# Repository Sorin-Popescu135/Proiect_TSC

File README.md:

# OpenBook Project

## Overview
The OpenBook Project uses the **ESP32-C6 WROOM** module, which features:
- **Processor:** RISC-V single-core  
- **Memory:** 512 KB SRAM  
- **Connectivity:** Wi-Fi 6, Bluetooth 5, IEEE 802.15.4  
- **Interfaces:** GPIO, SPI, I2C, USB 2.0  

## Diagram

## ESP32-C6 Pin Descriptions

### Buttons
- **pin 3** → RESET  
- **pin 15** → IO/BOOT  
- **pin 23** → IO/RESET  

### Battery Level
- **pin 20** → pin 7 (SCL)  
- **pin 8** → pin 19 (SDA)  

### USB-C Connector & ESD Protection
- **pin 14** → pin 1 (USB_D+)  
- **pin 13** → pin 3 (USB_D-)  

### SD Card
- **pin 4** → pin 2 (SS_SD)  
- **pin 6** → pin 5 (SCK)  
- **pin 7** → pin 3 (MOSI)  
- **pin 27** → pin 7 (MISO)  

### BME688 Sensor
- **pin 17** → pin 2, 6, 8 (I2C_PW)  
- **pin 19** → pin 3 (SDA)  
- **pin 20** → pin 4 (SCL)  

### RTC Module DS3231SN
- **pin 8** → pin 3 (INT_RTC)  
- **pin 9** → pin 1 (32KHZ)  
- **pin 16** → pin 4 (RTC_RST)  
- **pin 19** → pin 15 (SDA)  
- **pin 20** → pin 16 (SCL)

## Hardware Description

| Part              | Description                                     |
|-------------------|-------------------------------------------------|
| DS3231SN          | -> high accuracy RTC                            |
| MAX17048G+T10     | -> battery fuel gauge                           |
| W25Q512JVEIQ      | -> serial NOR flash memory                      |
| FH34SRJ24S05SH99  | -> FFC connector                                |
| SI1308EDL-T1-GE3  | -> N-channel MOSFET                             |
| MCP73831          |-> charge management controller, single-cell     |
| USB4110           | -> USB 2.0 Type C connector                     |
| CPH3225A          | -> chip-type electric double-layer capacitor    |
| MBR0530           | -> surface-mount Schottky rectifier diode       |
| BME688            | -> environmental sensor                         |
| XC6220A331MR-G    | -> high-speed, low-dropout voltage regulator    |

## Bill of Materials

| Component Name       | Price (euro) | Link                                                                                                  |
|----------------------|--------------|--------------------------------------------------------------------------------------------------------|
| DS3231SN             | 14.91        | [Mouser](https://ro.mouser.com/ProductDetail/Analog-Devices-Maxim-Integrated/DS3231SN?qs=1eQvB6Dk1vhUlr8%2FOrV0Fw%3D%3D)  |
| MAX17048G+T10        | 4.28         | [Mouser](https://eu.mouser.com/ProductDetail/Analog-Devices-Maxim-Integrated/MAX17048G%2bT10?qs=D7PJwyCwLAoGnnn8jEPRBQ%3D%3D)    |
| W25Q512JVEIQ         | 5.84         | [Mouser](https://eu.mouser.com/ProductDetail/Winbond/W25Q512JVEIQ?qs=l7cgNqFNU1jw6svr3at6tA%3D%3D)    |
| FH34SRJ24S05SH99     | 2.60         | [Mouser](https://eu.mouser.com/ProductDetail/Hirose-Connector/FH34SRJ-24S-0.5SH99?qs=vcbW%252B4%252BSTIpKBl5ap9J8Fw%3D%3D)        |
| SI1308EDL-T1-GE3     | 0.41         | [Mouser](https://eu.mouser.com/ProductDetail/Vishay-Semiconductors/SI1308EDL-T1-GE3?qs=bX1%252BNvsK%2FBramh9tgpOaEw%3D%3D)         |
| MCP73831             | 0.70         | [Mouser](https://eu.mouser.com/ProductDetail/Microchip-Technology/MCP73831T-2ACI-OT?qs=yUQqVecv4qvbBQBGbHx0Mw%3D%3D)             |
| USB4110              | 1.18         | [Mouser](https://eu.mouser.com/ProductDetail/GCT/USB4110-GF-A?qs=KUoIvG%2F9IlYiZvIXQjyJeA%3D%3D)                          |
| CPH3225A             | 2.23         | [Mouser](https://eu.mouser.com/ProductDetail/Seiko-Semiconductors/CPH3225A?qs=3etwrb1wR%252BhUOph6lAO7eg%3D%3D)           |
| MBR0530              | 0.14         | [Mouser](https://eu.mouser.com/ProductDetail/Micro-Commercial-Components-MCC/MBR0530-TP?qs=KFo7JewZbUECRHkxGanrdg%3D%3D)        |
| BME688               | 9.86         | [Mouser](https://eu.mouser.com/ProductDetail/Bosch-Sensortec/BME688?qs=IS%252B4QmGtzzqQoVDscqwx3A%3D%3D)                    |
| XC6220A331MR-G       | 1.46         | [Mouser](https://eu.mouser.com/ProductDetail/Torex-Semiconductor/XC6220A331MR-G?qs=AsjdqWjXhJ8ZSWznL1J0gg%3D%3D)            |

## Additional Photos

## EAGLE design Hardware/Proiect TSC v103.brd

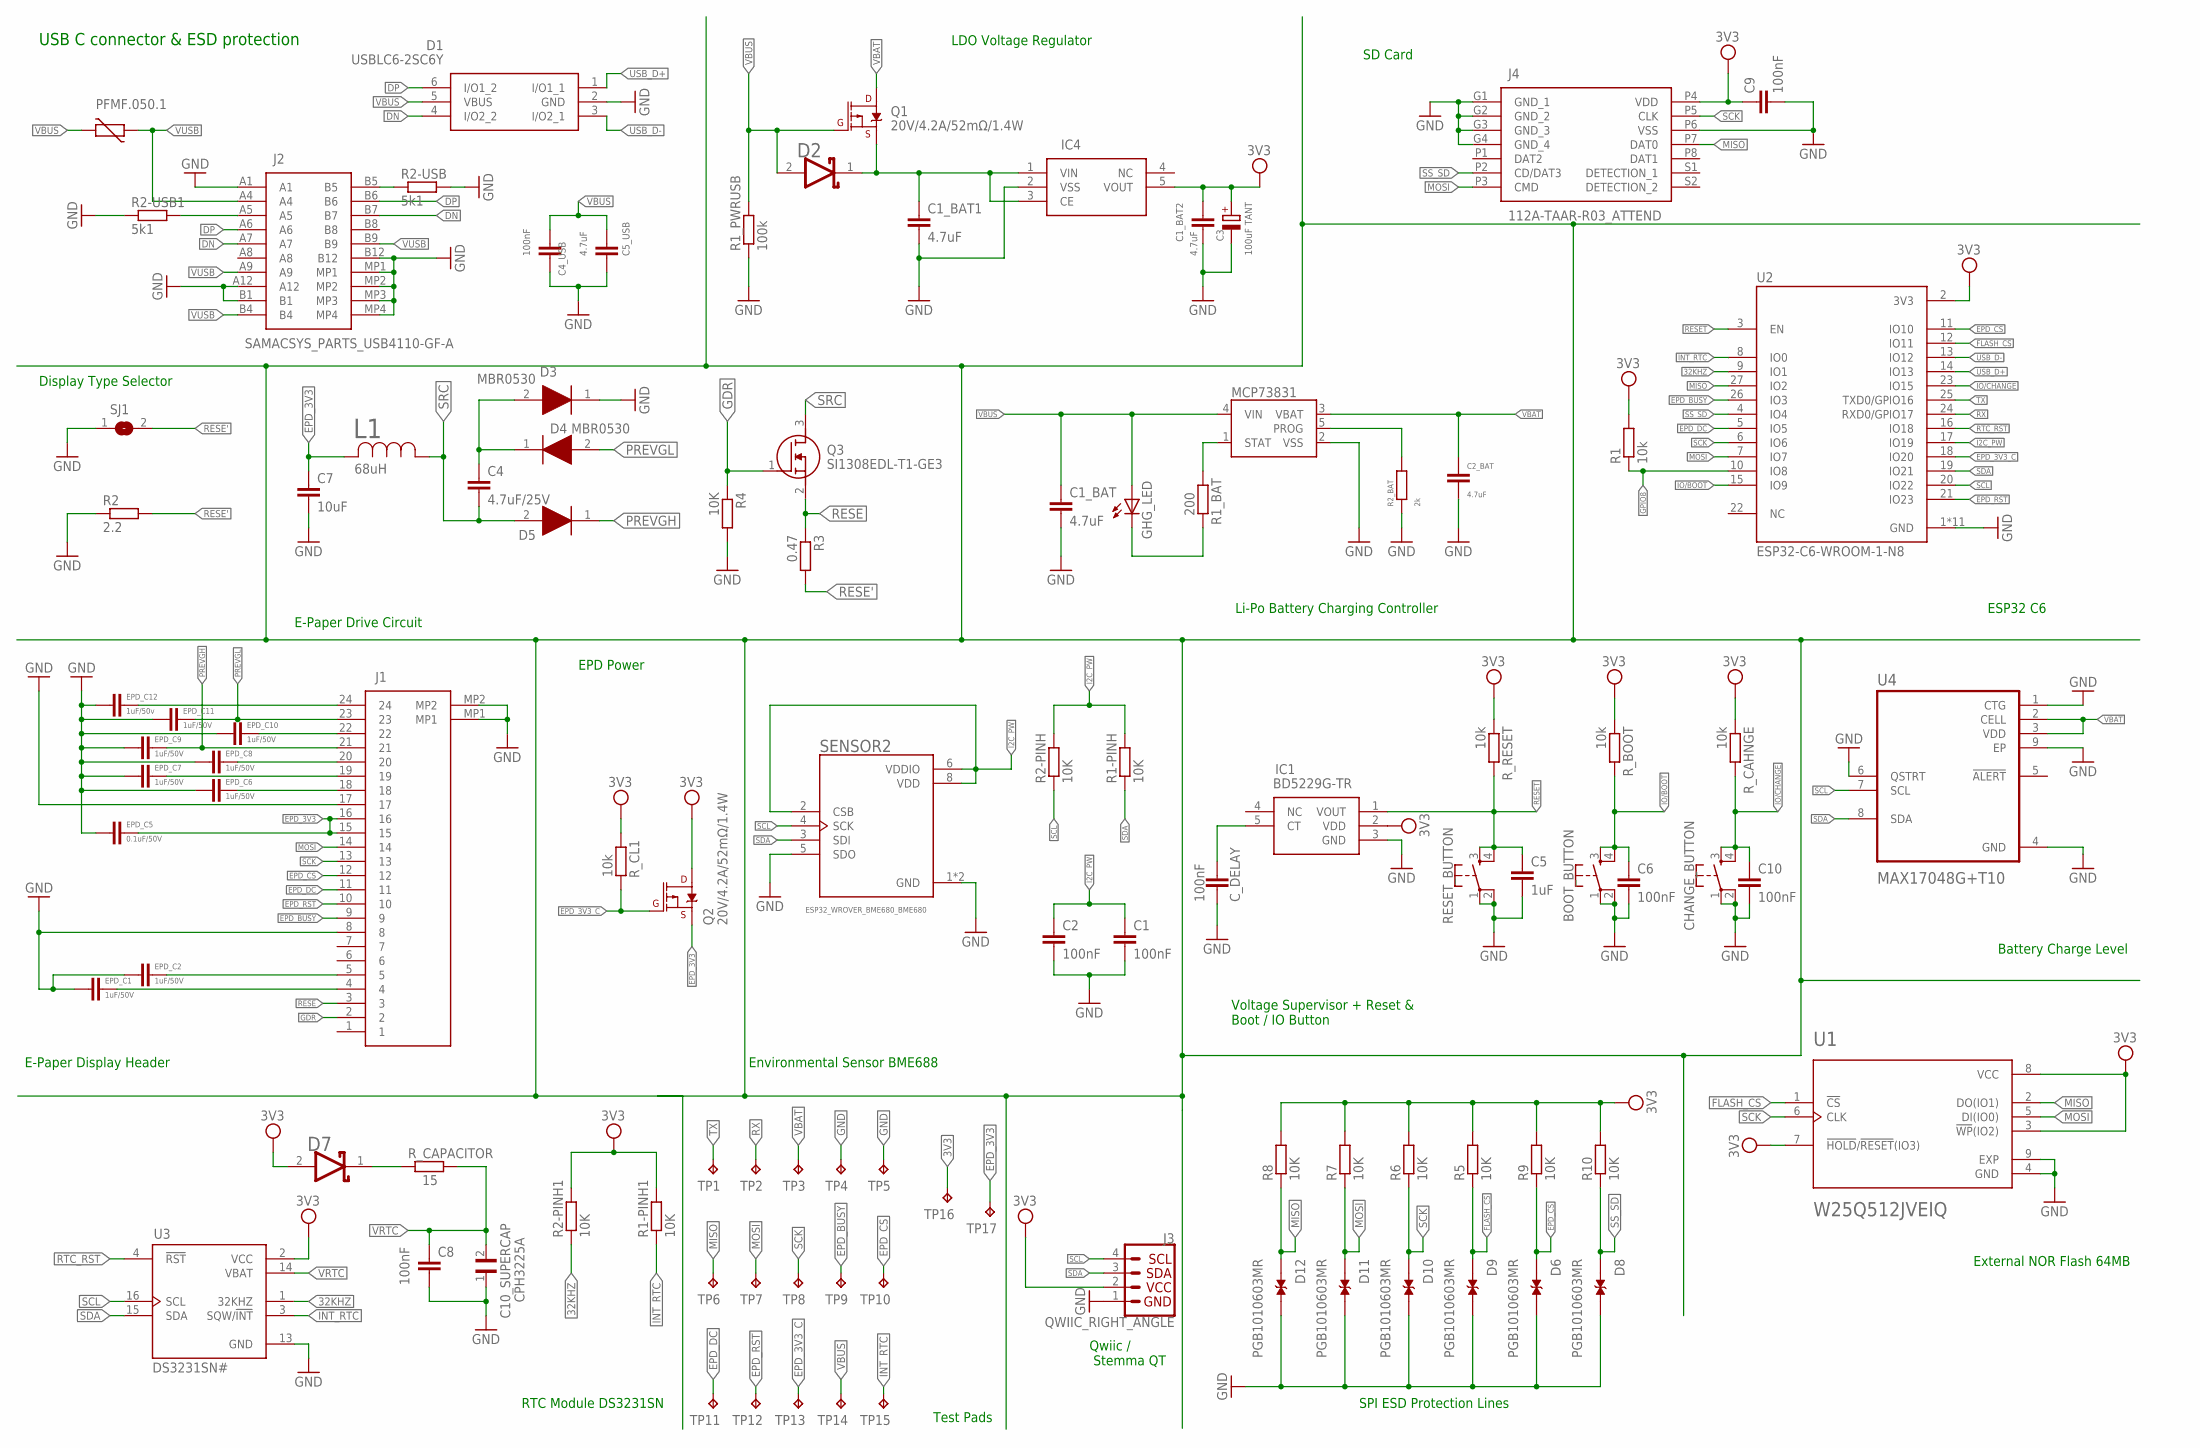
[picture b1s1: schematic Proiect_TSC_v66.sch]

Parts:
BOOT_BUTTON: BUTTON_CUSYOMV1; MYBUTTON
C1, C2, C9: 100nF; EAGLE-LTSPICE_C0402
C1_BAT, C2_BAT, C5_USB: 4.7uF; ESP32_WROVER_EAGLE-LTSPICE_C0402
C1_BAT1, C1_BAT2: 4.7uF; EAGLE-LTSPICE_C0402
C3: 100uF TANT; RCL_CT3528
C4: 4.7uF/25V; ESP32_WROVER_EAGLE-LTSPICE_C0402
C4_USB, C6, C8, C10: 100nF; ESP32_WROVER_EAGLE-LTSPICE_C0402
C5: 1uF; ESP32_WROVER_EAGLE-LTSPICE_C0402
C7: 10uF; EAGLE-LTSPICE_C0402
C10_SUPERCAP: CPH3225A; CAPCP3225X100N
CHANGE_BUTTON: BUTTON_CUSYOMV1; MYBUTTON
C_DELAY: 100nF; EAGLE-LTSPICE_C0402
D1: USBLC6-2SC6Y; SOT95P280X145-6N
D2, D7: ESP32_WROVER_AVX---SD0805S020S1R0_AVX_SD0805S020S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; ESP32_WROVER_AVX---SD0805S020S1R0_AVX_SD0805S020S1R0_0
D3, D4, D5: MBR0530; SOD3716X135N
D6, D8, D9, D10, D11, D12: PGB1010603MR; DIOC1608X36N
EPD_C1, EPD_C2, EPD_C6, EPD_C7, EPD_C8, EPD_C9, EPD_C10, EPD_C11: 1uF/50V; EAGLE-LTSPICE_C0402
EPD_C5: 0.1uF/50V; EAGLE-LTSPICE_C0402
EPD_C12: 1uF/50v; EAGLE-LTSPICE_C0402
GHG_LED: ADAFRUIT_LEDCHIP-LED0603; ADAFRUIT_CHIP-LED0603
IC1: BD5229G-TR; SOT95P280X125-5N
IC4: XC6220A331MR-G; SOT95P280X120-5N
J1: FH34SRJ-24S-0.5SH_99_; FH34SRJ24S05SH99
J2: SAMACSYS_PARTS_USB4110-GF-A; SAMACSYS_PARTS_USB4110GFA
J3: QWIIC_RIGHT_ANGLE; JST04_1MM_RA
J4: 112A-TAAR-R03_ATTEND; 112ATAARR03ATTEND
L1: 68uH; IND_4828-WE-TPC_WRE
MCP73831: ESP32_WROVER_SPARKFUN-IC-POWER_MCP73831; ESP32_WROVER_SPARKFUN-IC-POWER_SOT23-5
PFMF.050.1: ESP32C6_VARISTORCN1812; ESP32C6_VARISTOR_CT/CN1812
Q1, Q2: 20V/4.2A/52mΩ/1.4W; ESP32_WROVER_SPARKFUN-DISCRETESEMI_SOT23-3
Q3: SI1308EDL-T1-GE3; SOT65P210X110-3N
R1: 10k; ESP32_WROVER_EAGLE-LTSPICE_R0402
R1-PINH, R1-PINH1, R2-PINH, R2-PINH1, R4, R5, R6, R7, R8, R9, R10: 10K; ESP32_WROVER_EAGLE-LTSPICE_R0402
R1_BAT: 200; ESP32_WROVER_EAGLE-LTSPICE_R0402
R1_PWRUSB: 100k; ESP32_WROVER_EAGLE-LTSPICE_R0402
R2: 2.2; ESP32_WROVER_EAGLE-LTSPICE_R0402
R2-USB, R2-USB1: 5k1; ESP32_WROVER_EAGLE-LTSPICE_R0402
R2_BAT: 2k; ESP32_WROVER_EAGLE-LTSPICE_R0402
R3: 0.47; ESP32_WROVER_EAGLE-LTSPICE_R0402
RESET_BUTTON: BUTTON_CUSYOMV1; MYBUTTON
R_BOOT: 10k; ESP32_WROVER_EAGLE-LTSPICE_R0402
R_CAHNGE: 10k; ESP32_WROVER_EAGLE-LTSPICE_R0402
R_CAPACITOR: 15; ESP32_WROVER_EAGLE-LTSPICE_R0402
R_CL1: 10k; ESP32_WROVER_EAGLE-LTSPICE_R0402
R_RESET: 10k; ESP32_WROVER_EAGLE-LTSPICE_R0402
SENSOR2: ESP32_WROVER_BME680_BME680; ESP32_WROVER_BME680_PSON80P300X300X100-8N
SJ1: SJ
TP1, TP2, TP3, TP4, TP5, TP6, TP7, TP8, TP9, TP10, TP11, TP12, TP13, TP14, TP15, TP16, TP17: TPTP20R; TP20R
U1: W25Q512JVEIQ; SON127P600X800X80-9N
U2: ESP32-C6-WROOM-1-N8; XCVR_ESP32-C6-WROOM-1-N8
U3: DS3231SN#; SOIC127P1032X265-16N
U4: MAX17048G+T10; SON50P200X200X80-9N

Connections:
3V3: C1_BAT2.1, C3.+, C9.1, D7.2 (ANODE), IC1.2 (VDD), IC4.5 (VOUT), J3.2, J4.P4 (VDD), Q2.3 (D), R1.2, R1-PINH1.2, R2-PINH1.2, R5.2, R6.2, R7.2, R8.2, R9.2, R10.2, R_BOOT.1, R_CAHNGE.1, R_CL1.1, R_RESET.1, TP16.TP, U1.3 (!WP!(IO2)), U1.7 (!HOLD!/!RESET!(IO3)), U1.8 (VCC), U2.2 (3V3), U3.2 (VCC)
32KHZ: R2-PINH1.1, U2.9 (IO1), U3.1 (32KHZ)
DN: D1.4 (I/O2_2), J2.A7, J2.B7
DP: D1.6 (I/O1_2), J2.A6, J2.B6
EPD_3V3: C7.1, EPD_C5.1, J1.15, J1.16, L1.2, Q2.2 (S), TP17.TP
EPD_3V3_C: Q2.1 (G), R_CL1.2, TP13.TP, U2.18 (IO20)
EPD_BUSY: J1.9, TP9.TP, U2.26 (IO3)
EPD_CS: D6.1, J1.12, R9.1, TP10.TP, U2.11 (IO10)
EPD_DC: J1.11, TP11.TP, U2.5 (IO5)
EPD_RST: J1.10, TP12.TP, U2.21 (IO23)
FLASH_CS: D9.1, R5.1, U1.1 (!CS), U2.12 (IO11)
GDR: J1.2, Q3.1 (G), R4.1
GND: BOOT_BUTTON.1, BOOT_BUTTON.2, C1.2, C1_BAT.2, C1_BAT1.2, C1_BAT2.2, C2.2, C2_BAT.2, C3.-, C4_USB.2, C5.2, C5_USB.2, C6.2, C7.2, C8.2, C9.2, C10.2, C10_SUPERCAP.1, CHANGE_BUTTON.1, CHANGE_BUTTON.2, C_DELAY.2, D1.2 (GND), D3.1 (K), D6.2, D8.2, D9.2, D10.2, D11.2, D12.2, EPD_C1.2, EPD_C2.2, EPD_C5.2, EPD_C6.2, EPD_C7.2, EPD_C8.2, EPD_C9.2, EPD_C10.2, EPD_C11.2, EPD_C12.2, IC1.3 (GND), IC4.2 (VSS), J1.8, J1.17, J1.MP1, J1.MP2, J2.A1, J2.A12, J2.B1, J2.B12, J2.MP1, J2.MP2, J2.MP3, J2.MP4, J3.1, J4.G1 (GND_1), J4.G2 (GND_2), J4.G3 (GND_3), J4.G4 (GND_4), J4.P6 (VSS), MCP73831.2 (VSS), R1_PWRUSB.1, R2.1, R2-USB.2, R2-USB1.1, R2_BAT.1, R4.2, RESET_BUTTON.1, RESET_BUTTON.2, SENSOR2.1 (GND), SENSOR2.5 (SDO), SENSOR2.7 (GND), SJ1.1, TP4.TP, TP5.TP, U1.4 (GND), U1.9 (EXP), U2.1 (GND), U2.28 (GND), U2.29_1 (GND), U2.29_2 (GND), U2.29_3 (GND), U2.29_4 (GND), U2.29_5 (GND), U2.29_6 (GND), U2.29_7 (GND), U2.29_8 (GND), U2.29_9 (GND), U3.13 (GND), U4.1 (CTG), U4.4 (GND), U4.6 (QSTRT), U4.9 (EP)
GPIO8: R1.1, U2.10 (IO8)
I2C_PW: C1.1, C2.1, R1-PINH.2, R2-PINH.2, SENSOR2.2 (CSB), SENSOR2.6 (VDDIO), SENSOR2.8 (VDD), U2.17 (IO19)
INT_RTC: R1-PINH1.1, TP15.TP, U2.8 (IO0), U3.3 (SQW/!INT)
IO/BOOT: BOOT_BUTTON.3, BOOT_BUTTON.4, C6.1, R_BOOT.2, U2.15 (IO9)
IO/CHANGE: C10.1, CHANGE_BUTTON.3, CHANGE_BUTTON.4, R_CAHNGE.2, U2.23 (IO15)
MISO: D12.1, J4.P7 (DAT0), R8.1, TP6.TP, U1.2 (DO(IO1)), U2.27 (IO2)
MOSI: D11.1, J1.14, J4.P3 (CMD), R7.1, TP7.TP, U1.5 (DI(IO0)), U2.7 (IO7)
unnamed: J2.B5, R2-USB.1
unnamed: J2.A5, R2-USB1.2
unnamed: C1_BAT1.1, D2.1 (CATHODE), IC4.1 (VIN), IC4.3 (CE), Q1.2 (S)
unnamed: MCP73831.5 (PROG), R2_BAT.2
unnamed: MCP73831.1 (STAT), R1_BAT.1
unnamed: GHG_LED.C, R1_BAT.2
unnamed: EPD_C12.1, J1.24
unnamed: EPD_C10.1, J1.22
unnamed: EPD_C8.1, J1.20
unnamed: EPD_C7.1, J1.19
unnamed: EPD_C6.1, J1.18
unnamed: EPD_C2.1, J1.5
unnamed: C_DELAY.1, IC1.5 (CT)
unnamed: EPD_C1.1, J1.4
unnamed: D7.1 (CATHODE), R_CAPACITOR.1
unnamed: C4.1, D3.2 (A), D4.1 (K)
PREVGH: D5.1 (K), EPD_C9.1, J1.21
PREVGL: D4.2 (A), EPD_C11.1, J1.23
RESE: J1.3, Q3.2 (S), R3.1
RESE': R2.2, R3.2, SJ1.2
RESET: C5.1, IC1.1 (VOUT), RESET_BUTTON.3, RESET_BUTTON.4, R_RESET.2, U2.3 (EN)
RTC_RST: U2.16 (IO18), U3.4 (!RST)
RX: TP2.TP, U2.24 (RXD0/GPIO17)
SCK: D10.1, J1.13, J4.P5 (CLK), R6.1, TP8.TP, U1.6 (CLK), U2.6 (IO6)
SCL: J3.4, R2-PINH.1, SENSOR2.4 (SCK), U2.20 (IO22), U3.16 (SCL), U4.7 (SCL)
SDA: J3.3, R1-PINH.1, SENSOR2.3 (SDI), U2.19 (IO21), U3.15 (SDA), U4.8 (SDA)
SRC: C4.2, D5.2 (A), L1.1, Q3.3 (D)
SS_SD: D8.1, J4.P2 (CD/DAT3), R10.1, U2.4 (IO4)
TX: TP1.TP, U2.25 (TXD0/GPIO16)
USB_D+: D1.1 (I/O1_1), U2.14 (IO13)
USB_D-: D1.3 (I/O2_1), U2.13 (IO12)
VBAT: C2_BAT.1, MCP73831.3 (VBAT), Q1.3 (D), TP3.TP, U4.2 (CELL), U4.3 (VDD)
VBUS: C1_BAT.1, C4_USB.1, C5_USB.1, D1.5 (VBUS), D2.2 (ANODE), GHG_LED.A, MCP73831.4 (VIN), PFMF.050.1.2, Q1.1 (G), R1_PWRUSB.2, TP14.TP
VRTC: C8.1, C10_SUPERCAP.2, R_CAPACITOR.2, U3.14 (VBAT)
VUSB: J2.A4, J2.A9, J2.B4, J2.B9, PFMF.050.1.1

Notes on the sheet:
USB C connector & ESD protection
LDO Voltage Regulator
SD Card
Display Type Selector
E-Paper Drive Circuit
Li-Po Battery Charging Controller
ESP32 C6
E-Paper Display Header
EPD Power
Environmental Sensor BME688
Voltage Supervisor + Reset & Boot / IO Button
Battery Charge Level
RTC Module DS3231SN
SPI ESD Protection Lines
External NOR Flash 64MB
Qwiic / Stemma QT
Test Pads

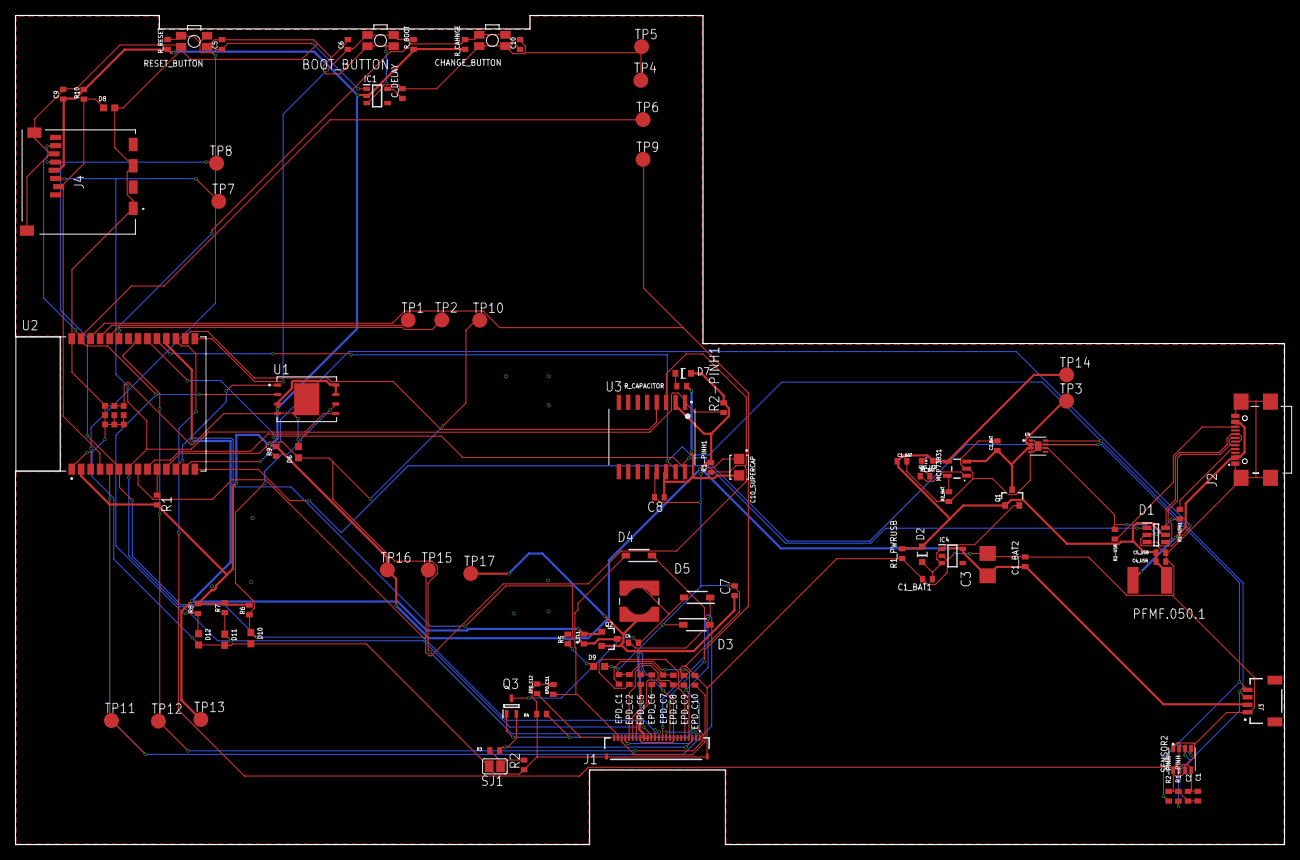
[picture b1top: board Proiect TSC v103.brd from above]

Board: 2 copper layers, 170.2 x 111.2 mm, 103 parts (0 on the bottom side), 55 nets.

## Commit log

2025-04-06 Create LICENSE
2025-04-06 1st big commit
2025-04-11 Commit solving the issues

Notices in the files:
parts and their libraries:
COPYRIGHT: Copyright (C) 2024 Ultra Librarian. All rights reserved.
